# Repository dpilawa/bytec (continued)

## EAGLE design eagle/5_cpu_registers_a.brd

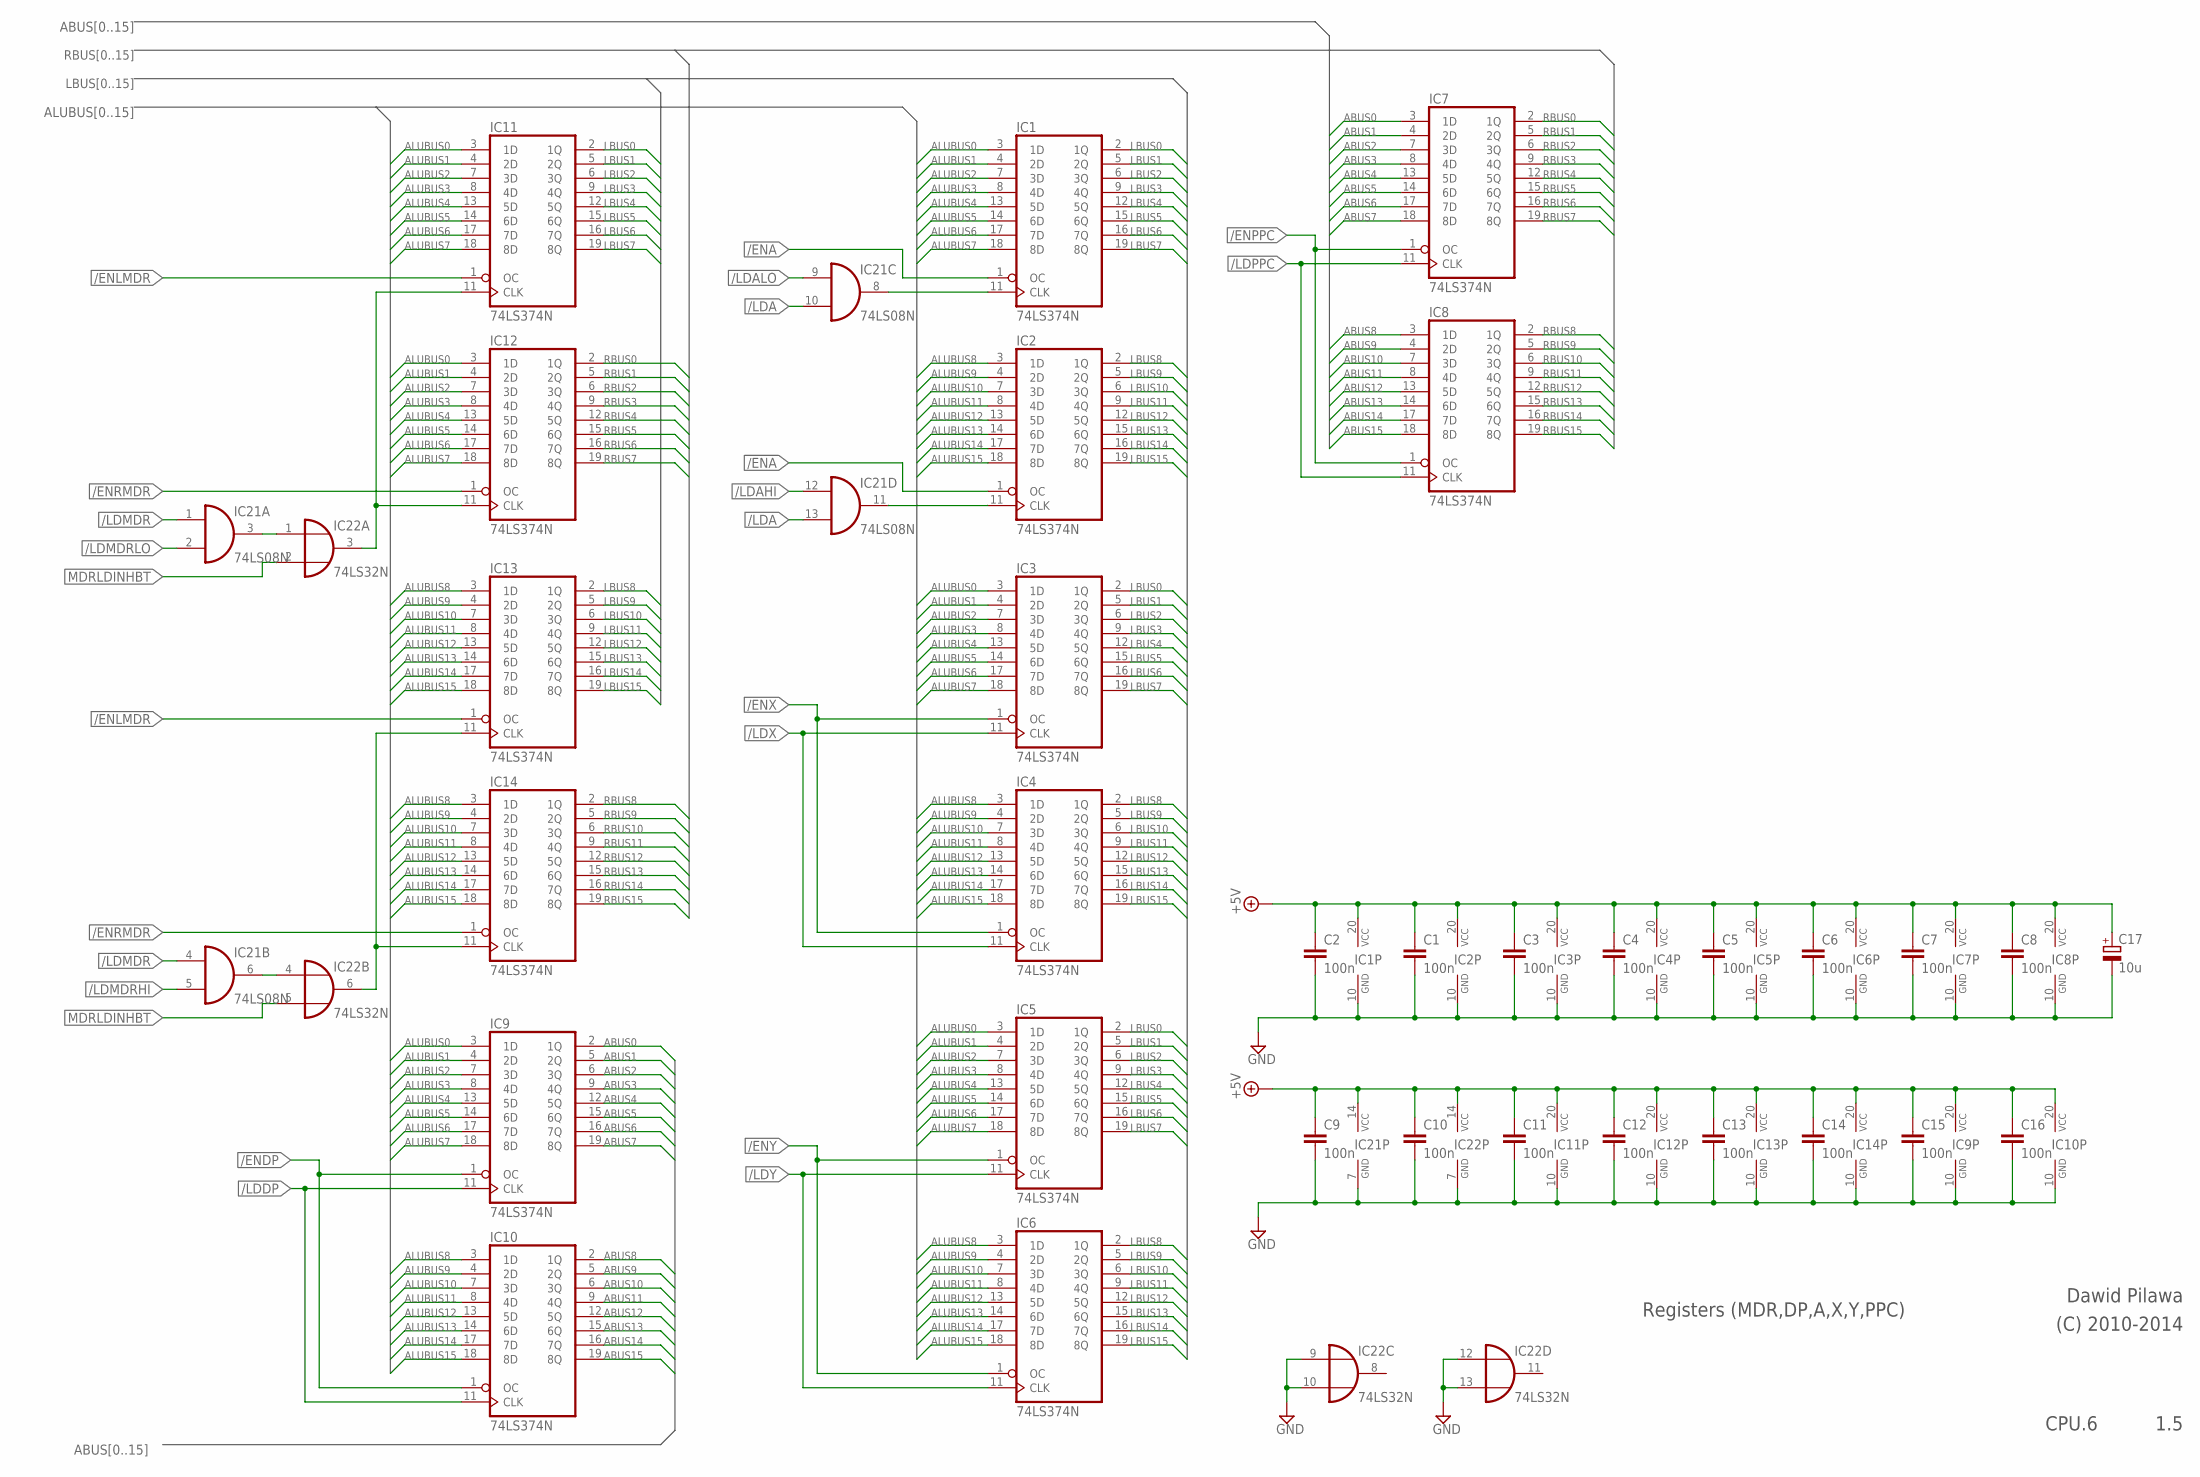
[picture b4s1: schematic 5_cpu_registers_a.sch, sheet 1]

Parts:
C1, C2, C3, C4, C5, C6, C7, C8, C9, C10, C11, C12, C13, C14, C15, C16: 100n; C050-024X044
C17: 10u; E2,5-6
IC1, IC2, IC3, IC4, IC5, IC6, IC7, IC8, IC9, IC10, IC11, IC12, IC13, IC14: 74LS374N; DIL20
IC21: 74LS08N; DIL14
IC22: 74LS32N; DIL14

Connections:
+5V: C1.1, C2.1, C3.1, C4.1, C5.1, C6.1, C7.1, C8.1, C9.1, C10.1, C11.1, C12.1, C13.1, C14.1, C15.1, C16.1, C17.+, IC1.20 (VCC), IC2.20 (VCC), IC3.20 (VCC), IC4.20 (VCC), IC5.20 (VCC), IC6.20 (VCC), IC7.20 (VCC), IC8.20 (VCC), IC9.20 (VCC), IC10.20 (VCC), IC11.20 (VCC), IC12.20 (VCC), IC13.20 (VCC), IC14.20 (VCC), IC21.14 (VCC), IC22.14 (VCC); also elsewhere on the board
/ENA: IC1.1 (OC), IC2.1 (OC); also elsewhere on the board
/ENDP: IC9.1 (OC), IC10.1 (OC); also elsewhere on the board
/ENLMDR: IC11.1 (OC), IC13.1 (OC); also elsewhere on the board
/ENRMDR: IC12.1 (OC), IC14.1 (OC); also elsewhere on the board
/ENX: IC3.1 (OC), IC4.1 (OC); also elsewhere on the board
/ENY: IC5.1 (OC), IC6.1 (OC); also elsewhere on the board
/LDA: IC21.10 (I1), IC21.13 (I1); also elsewhere on the board
/LDAHI: IC21.12 (I0); also elsewhere on the board
/LDALO: IC21.9 (I0); also elsewhere on the board
/LDDP: IC9.11 (CLK), IC10.11 (CLK); also elsewhere on the board
/LDMDR: IC21.1 (I0), IC21.4 (I0); also elsewhere on the board
/LDMDRHI: IC21.5 (I1); also elsewhere on the board
/LDMDRLO: IC21.2 (I1); also elsewhere on the board
/LDX: IC3.11 (CLK), IC4.11 (CLK); also elsewhere on the board
/LDY: IC5.11 (CLK), IC6.11 (CLK); also elsewhere on the board
ABUS0: IC7.3 (1D), IC9.2 (1Q); also elsewhere on the board
ABUS1: IC7.4 (2D), IC9.5 (2Q); also elsewhere on the board
ABUS2: IC7.7 (3D), IC9.6 (3Q); also elsewhere on the board
ABUS3: IC7.8 (4D), IC9.9 (4Q); also elsewhere on the board
ABUS4: IC7.13 (5D), IC9.12 (5Q); also elsewhere on the board
ABUS5: IC7.14 (6D), IC9.15 (6Q); also elsewhere on the board
ABUS6: IC7.17 (7D), IC9.16 (7Q); also elsewhere on the board
ABUS7: IC7.18 (8D), IC9.19 (8Q); also elsewhere on the board
ABUS8: IC8.3 (1D), IC10.2 (1Q); also elsewhere on the board
ABUS9: IC8.4 (2D), IC10.5 (2Q); also elsewhere on the board
ABUS10: IC8.7 (3D), IC10.6 (3Q); also elsewhere on the board
ABUS11: IC8.8 (4D), IC10.9 (4Q); also elsewhere on the board
ABUS12: IC8.13 (5D), IC10.12 (5Q); also elsewhere on the board
ABUS13: IC8.14 (6D), IC10.15 (6Q); also elsewhere on the board
ABUS14: IC8.17 (7D), IC10.16 (7Q); also elsewhere on the board
ABUS15: IC8.18 (8D), IC10.19 (8Q); also elsewhere on the board
ALUBUS0: IC1.3 (1D), IC3.3 (1D), IC5.3 (1D), IC9.3 (1D), IC11.3 (1D), IC12.3 (1D); also elsewhere on the board
ALUBUS1: IC1.4 (2D), IC3.4 (2D), IC5.4 (2D), IC9.4 (2D), IC11.4 (2D), IC12.4 (2D); also elsewhere on the board
ALUBUS2: IC1.7 (3D), IC3.7 (3D), IC5.7 (3D), IC9.7 (3D), IC11.7 (3D), IC12.7 (3D); also elsewhere on the board
ALUBUS3: IC1.8 (4D), IC3.8 (4D), IC5.8 (4D), IC9.8 (4D), IC11.8 (4D), IC12.8 (4D); also elsewhere on the board
ALUBUS4: IC1.13 (5D), IC3.13 (5D), IC5.13 (5D), IC9.13 (5D), IC11.13 (5D), IC12.13 (5D); also elsewhere on the board
ALUBUS5: IC1.14 (6D), IC3.14 (6D), IC5.14 (6D), IC9.14 (6D), IC11.14 (6D), IC12.14 (6D); also elsewhere on the board
ALUBUS6: IC1.17 (7D), IC3.17 (7D), IC5.17 (7D), IC9.17 (7D), IC11.17 (7D), IC12.17 (7D); also elsewhere on the board
ALUBUS7: IC1.18 (8D), IC3.18 (8D), IC5.18 (8D), IC9.18 (8D), IC11.18 (8D), IC12.18 (8D); also elsewhere on the board
ALUBUS8: IC2.3 (1D), IC4.3 (1D), IC6.3 (1D), IC10.3 (1D), IC13.3 (1D), IC14.3 (1D); also elsewhere on the board
ALUBUS9: IC2.4 (2D), IC4.4 (2D), IC6.4 (2D), IC10.4 (2D), IC13.4 (2D), IC14.4 (2D); also elsewhere on the board
ALUBUS10: IC2.7 (3D), IC4.7 (3D), IC6.7 (3D), IC10.7 (3D), IC13.7 (3D), IC14.7 (3D); also elsewhere on the board
ALUBUS11: IC2.8 (4D), IC4.8 (4D), IC6.8 (4D), IC10.8 (4D), IC13.8 (4D), IC14.8 (4D); also elsewhere on the board
ALUBUS12: IC2.13 (5D), IC4.13 (5D), IC6.13 (5D), IC10.13 (5D), IC13.13 (5D), IC14.13 (5D); also elsewhere on the board
ALUBUS13: IC2.14 (6D), IC4.14 (6D), IC6.14 (6D), IC10.14 (6D), IC13.14 (6D), IC14.14 (6D); also elsewhere on the board
ALUBUS14: IC2.17 (7D), IC4.17 (7D), IC6.17 (7D), IC10.17 (7D), IC13.17 (7D), IC14.17 (7D); also elsewhere on the board
ALUBUS15: IC2.18 (8D), IC4.18 (8D), IC6.18 (8D), IC10.18 (8D), IC13.18 (8D), IC14.18 (8D); also elsewhere on the board
GND: C1.2, C2.2, C3.2, C4.2, C5.2, C6.2, C7.2, C8.2, C9.2, C10.2, C11.2, C12.2, C13.2, C14.2, C15.2, C16.2, C17.-, IC1.10 (GND), IC2.10 (GND), IC3.10 (GND), IC4.10 (GND), IC5.10 (GND), IC6.10 (GND), IC7.10 (GND), IC8.10 (GND), IC9.10 (GND), IC10.10 (GND), IC11.10 (GND), IC12.10 (GND), IC13.10 (GND), IC14.10 (GND), IC21.7 (GND), IC22.7 (GND), IC22.9 (I0), IC22.10 (I1), IC22.12 (I0), IC22.13 (I1); also elsewhere on the board
LBUS0: IC1.2 (1Q), IC3.2 (1Q), IC5.2 (1Q), IC11.2 (1Q); also elsewhere on the board
LBUS1: IC1.5 (2Q), IC3.5 (2Q), IC5.5 (2Q), IC11.5 (2Q); also elsewhere on the board
LBUS2: IC1.6 (3Q), IC3.6 (3Q), IC5.6 (3Q), IC11.6 (3Q); also elsewhere on the board
LBUS3: IC1.9 (4Q), IC3.9 (4Q), IC5.9 (4Q), IC11.9 (4Q); also elsewhere on the board
LBUS4: IC1.12 (5Q), IC3.12 (5Q), IC5.12 (5Q), IC11.12 (5Q); also elsewhere on the board
LBUS5: IC1.15 (6Q), IC3.15 (6Q), IC5.15 (6Q), IC11.15 (6Q); also elsewhere on the board
LBUS6: IC1.16 (7Q), IC3.16 (7Q), IC5.16 (7Q), IC11.16 (7Q); also elsewhere on the board
LBUS7: IC1.19 (8Q), IC3.19 (8Q), IC5.19 (8Q), IC11.19 (8Q); also elsewhere on the board
LBUS8: IC2.2 (1Q), IC4.2 (1Q), IC6.2 (1Q), IC13.2 (1Q); also elsewhere on the board
LBUS9: IC2.5 (2Q), IC4.5 (2Q), IC6.5 (2Q), IC13.5 (2Q); also elsewhere on the board
LBUS10: IC2.6 (3Q), IC4.6 (3Q), IC6.6 (3Q), IC13.6 (3Q); also elsewhere on the board
LBUS11: IC2.9 (4Q), IC4.9 (4Q), IC6.9 (4Q), IC13.9 (4Q); also elsewhere on the board
LBUS12: IC2.12 (5Q), IC4.12 (5Q), IC6.12 (5Q), IC13.12 (5Q); also elsewhere on the board
LBUS13: IC2.15 (6Q), IC4.15 (6Q), IC6.15 (6Q), IC13.15 (6Q); also elsewhere on the board
LBUS14: IC2.16 (7Q), IC4.16 (7Q), IC6.16 (7Q), IC13.16 (7Q); also elsewhere on the board
LBUS15: IC2.19 (8Q), IC4.19 (8Q), IC6.19 (8Q), IC13.19 (8Q); also elsewhere on the board
MDRLDINHBT: IC22.2 (I1), IC22.5 (I1); also elsewhere on the board
unnamed: IC11.11 (CLK), IC12.11 (CLK), IC22.3 (O)
unnamed: IC21.3 (O), IC22.1 (I0)
unnamed: IC21.6 (O), IC22.4 (I0)
unnamed: IC13.11 (CLK), IC14.11 (CLK), IC22.6 (O)
unnamed: IC1.11 (CLK), IC21.8 (O)
unnamed: IC2.11 (CLK), IC21.11 (O)
unnamed: IC7.1 (OC), IC8.1 (OC)
unnamed: IC7.11 (CLK), IC8.11 (CLK)
RBUS0: IC7.2 (1Q), IC12.2 (1Q); also elsewhere on the board
RBUS1: IC7.5 (2Q), IC12.5 (2Q); also elsewhere on the board
RBUS2: IC7.6 (3Q), IC12.6 (3Q); also elsewhere on the board
RBUS3: IC7.9 (4Q), IC12.9 (4Q); also elsewhere on the board
RBUS4: IC7.12 (5Q), IC12.12 (5Q); also elsewhere on the board
RBUS5: IC7.15 (6Q), IC12.15 (6Q); also elsewhere on the board
RBUS6: IC7.16 (7Q), IC12.16 (7Q); also elsewhere on the board
RBUS7: IC7.19 (8Q), IC12.19 (8Q); also elsewhere on the board
RBUS8: IC8.2 (1Q), IC14.2 (1Q); also elsewhere on the board
RBUS9: IC8.5 (2Q), IC14.5 (2Q); also elsewhere on the board
RBUS10: IC8.6 (3Q), IC14.6 (3Q); also elsewhere on the board
RBUS11: IC8.9 (4Q), IC14.9 (4Q); also elsewhere on the board
RBUS12: IC8.12 (5Q), IC14.12 (5Q); also elsewhere on the board
RBUS13: IC8.15 (6Q), IC14.15 (6Q); also elsewhere on the board
RBUS14: IC8.16 (7Q), IC14.16 (7Q); also elsewhere on the board
RBUS15: IC8.19 (8Q), IC14.19 (8Q); also elsewhere on the board

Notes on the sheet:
Registers (MDR,DP,A,X,Y,PPC)
Dawid Pilawa
(C) 2010-2014
CPU.6
1.5

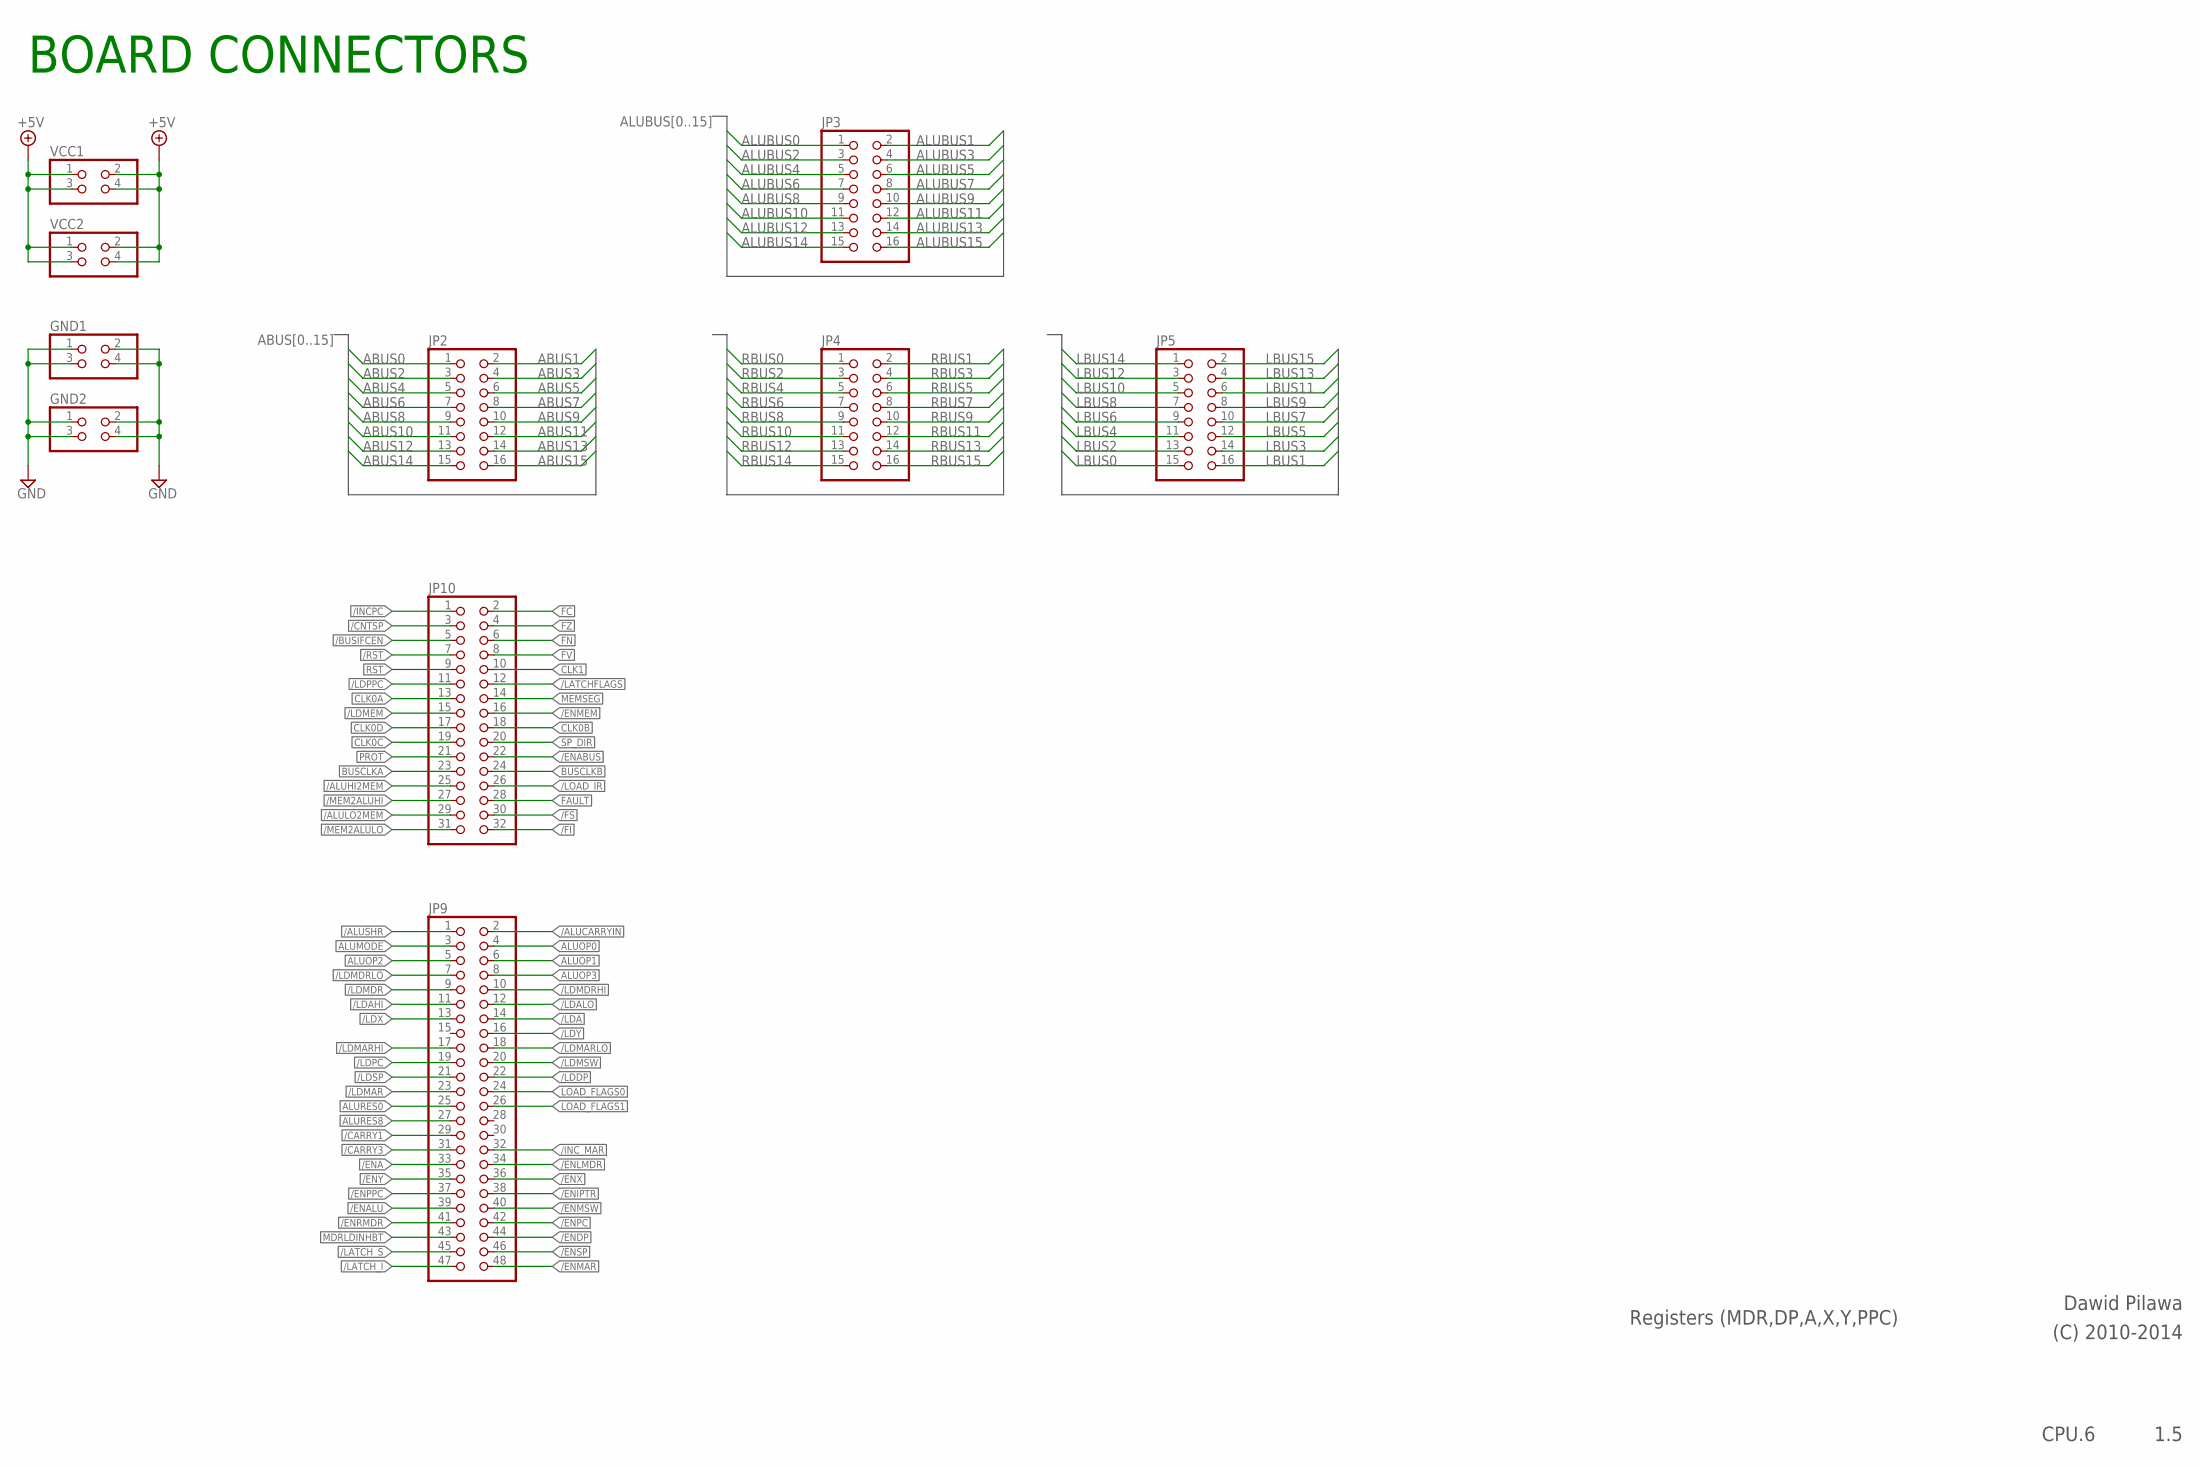
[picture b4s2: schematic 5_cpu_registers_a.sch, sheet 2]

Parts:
GND1, GND2: PINHD-2X2; 2X02
JP2, JP3, JP4, JP5: PINHD-2X8; 2X08
JP9: PINHD-2X24; 2X24
JP10: PINHD-2X16; 2X16
VCC1, VCC2: PINHD-2X2; 2X02

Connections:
+5V: VCC1.1, VCC1.2, VCC1.3, VCC1.4, VCC2.1, VCC2.2, VCC2.3, VCC2.4; also elsewhere on the board
/ALUCARRYIN: JP9.2
/ALUHI2MEM: JP10.25
/ALULO2MEM: JP10.29
/ALUSHR: JP9.1
/BUSIFCEN: JP10.5
/CARRY1: JP9.29
/CARRY3: JP9.31
/CNTSP: JP10.3
/ENA: JP9.33; also elsewhere on the board
/ENABUS: JP10.22
/ENALU: JP9.39
/ENDP: JP9.44; also elsewhere on the board
/ENIPTR: JP9.38
/ENLMDR: JP9.34; also elsewhere on the board
/ENMAR: JP9.48
/ENMEM: JP10.16
/ENMSW: JP9.40
/ENPC: JP9.42
/ENRMDR: JP9.41; also elsewhere on the board
/ENSP: JP9.46
/ENX: JP9.36; also elsewhere on the board
/ENY: JP9.35; also elsewhere on the board
/FI: JP10.32
/FS: JP10.30
/INCPC: JP10.1
/INC_MAR: JP9.32
/LATCHFLAGS: JP10.12
/LATCH_I: JP9.47
/LATCH_S: JP9.45
/LDA: JP9.14; also elsewhere on the board
/LDAHI: JP9.11; also elsewhere on the board
/LDALO: JP9.12; also elsewhere on the board
/LDDP: JP9.22; also elsewhere on the board
/LDMAR: JP9.23
/LDMARHI: JP9.17
/LDMARLO: JP9.18
/LDMDR: JP9.9; also elsewhere on the board
/LDMDRHI: JP9.10; also elsewhere on the board
/LDMDRLO: JP9.7; also elsewhere on the board
/LDMEM: JP10.15
/LDMSW: JP9.20
/LDPC: JP9.19
/LDSP: JP9.21
/LDX: JP9.13; also elsewhere on the board
/LDY: JP9.16; also elsewhere on the board
/LOAD_IR: JP10.26
/MEM2ALUHI: JP10.27
/MEM2ALULO: JP10.31
/RST: JP10.7
ABUS0: JP2.1; also elsewhere on the board
ABUS1: JP2.2; also elsewhere on the board
ABUS2: JP2.3; also elsewhere on the board
ABUS3: JP2.4; also elsewhere on the board
ABUS4: JP2.5; also elsewhere on the board
ABUS5: JP2.6; also elsewhere on the board
ABUS6: JP2.7; also elsewhere on the board
ABUS7: JP2.8; also elsewhere on the board
ABUS8: JP2.9; also elsewhere on the board
ABUS9: JP2.10; also elsewhere on the board
ABUS10: JP2.11; also elsewhere on the board
ABUS11: JP2.12; also elsewhere on the board
ABUS12: JP2.13; also elsewhere on the board
ABUS13: JP2.14; also elsewhere on the board
ABUS14: JP2.15; also elsewhere on the board
ABUS15: JP2.16; also elsewhere on the board
ALUBUS0: JP3.1; also elsewhere on the board
ALUBUS1: JP3.2; also elsewhere on the board
ALUBUS2: JP3.3; also elsewhere on the board
ALUBUS3: JP3.4; also elsewhere on the board
ALUBUS4: JP3.5; also elsewhere on the board
ALUBUS5: JP3.6; also elsewhere on the board
ALUBUS6: JP3.7; also elsewhere on the board
ALUBUS7: JP3.8; also elsewhere on the board
ALUBUS8: JP3.9; also elsewhere on the board
ALUBUS9: JP3.10; also elsewhere on the board
ALUBUS10: JP3.11; also elsewhere on the board
ALUBUS11: JP3.12; also elsewhere on the board
ALUBUS12: JP3.13; also elsewhere on the board
ALUBUS13: JP3.14; also elsewhere on the board
ALUBUS14: JP3.15; also elsewhere on the board
ALUBUS15: JP3.16; also elsewhere on the board
ALUMODE: JP9.3
ALUOP0: JP9.4
ALUOP1: JP9.6
ALUOP2: JP9.5
ALUOP3: JP9.8
ALURES0: JP9.25
ALURES8: JP9.27
BUSCLKA: JP10.23
BUSCLKB: JP10.24
CLK0A: JP10.13
CLK0B: JP10.18
CLK0C: JP10.19
CLK0D: JP10.17
CLK1: JP10.10
FAULT: JP10.28
FC: JP10.2
FN: JP10.6
FV: JP10.8
FZ: JP10.4
GND: GND1.1, GND1.2, GND1.3, GND1.4, GND2.1, GND2.2, GND2.3, GND2.4; also elsewhere on the board
LBUS0: JP5.15; also elsewhere on the board
LBUS1: JP5.16; also elsewhere on the board
LBUS2: JP5.13; also elsewhere on the board
LBUS3: JP5.14; also elsewhere on the board
LBUS4: JP5.11; also elsewhere on the board
LBUS5: JP5.12; also elsewhere on the board
LBUS6: JP5.9; also elsewhere on the board
LBUS7: JP5.10; also elsewhere on the board
LBUS8: JP5.7; also elsewhere on the board
LBUS9: JP5.8; also elsewhere on the board
LBUS10: JP5.5; also elsewhere on the board
LBUS11: JP5.6; also elsewhere on the board
LBUS12: JP5.3; also elsewhere on the board
LBUS13: JP5.4; also elsewhere on the board
LBUS14: JP5.1; also elsewhere on the board
LBUS15: JP5.2; also elsewhere on the board
LOAD_FLAGS0: JP9.24
LOAD_FLAGS1: JP9.26
MDRLDINHBT: JP9.43; also elsewhere on the board
MEMSEG: JP10.14
PROT: JP10.21
RBUS0: JP4.1; also elsewhere on the board
RBUS1: JP4.2; also elsewhere on the board
RBUS2: JP4.3; also elsewhere on the board
RBUS3: JP4.4; also elsewhere on the board
RBUS4: JP4.5; also elsewhere on the board
RBUS5: JP4.6; also elsewhere on the board
RBUS6: JP4.7; also elsewhere on the board
RBUS7: JP4.8; also elsewhere on the board
RBUS8: JP4.9; also elsewhere on the board
RBUS9: JP4.10; also elsewhere on the board
RBUS10: JP4.11; also elsewhere on the board
RBUS11: JP4.12; also elsewhere on the board
RBUS12: JP4.13; also elsewhere on the board
RBUS13: JP4.14; also elsewhere on the board
RBUS14: JP4.15; also elsewhere on the board
RBUS15: JP4.16; also elsewhere on the board
RST: JP10.9
SP_DIR: JP10.20

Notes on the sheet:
Registers (MDR,DP,A,X,Y,PPC)
Dawid Pilawa
(C) 2010-2014
CPU.6
1.5
BOARD CONNECTORS

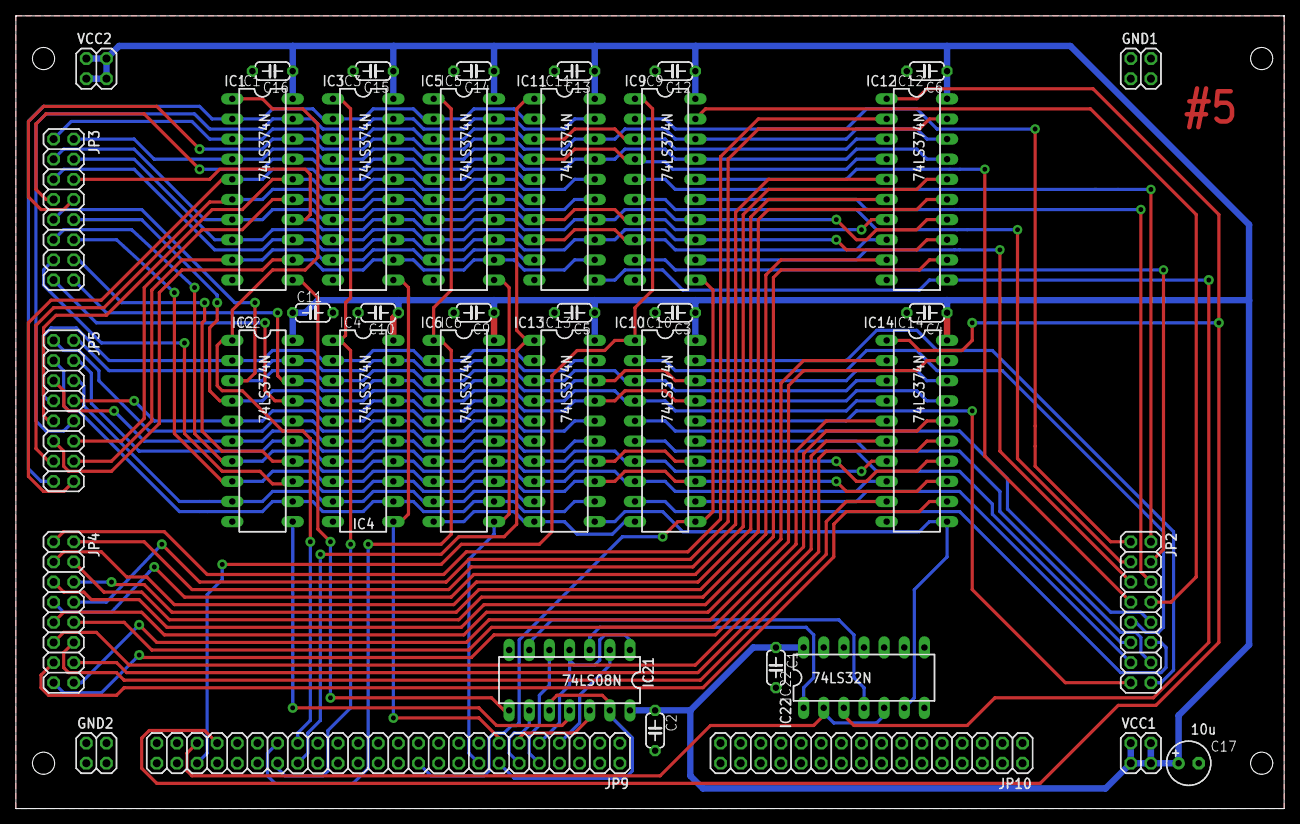
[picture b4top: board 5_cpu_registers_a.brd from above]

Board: 2 copper layers, 160.0 x 100.0 mm, 39 parts (0 on the bottom side), 88 nets.

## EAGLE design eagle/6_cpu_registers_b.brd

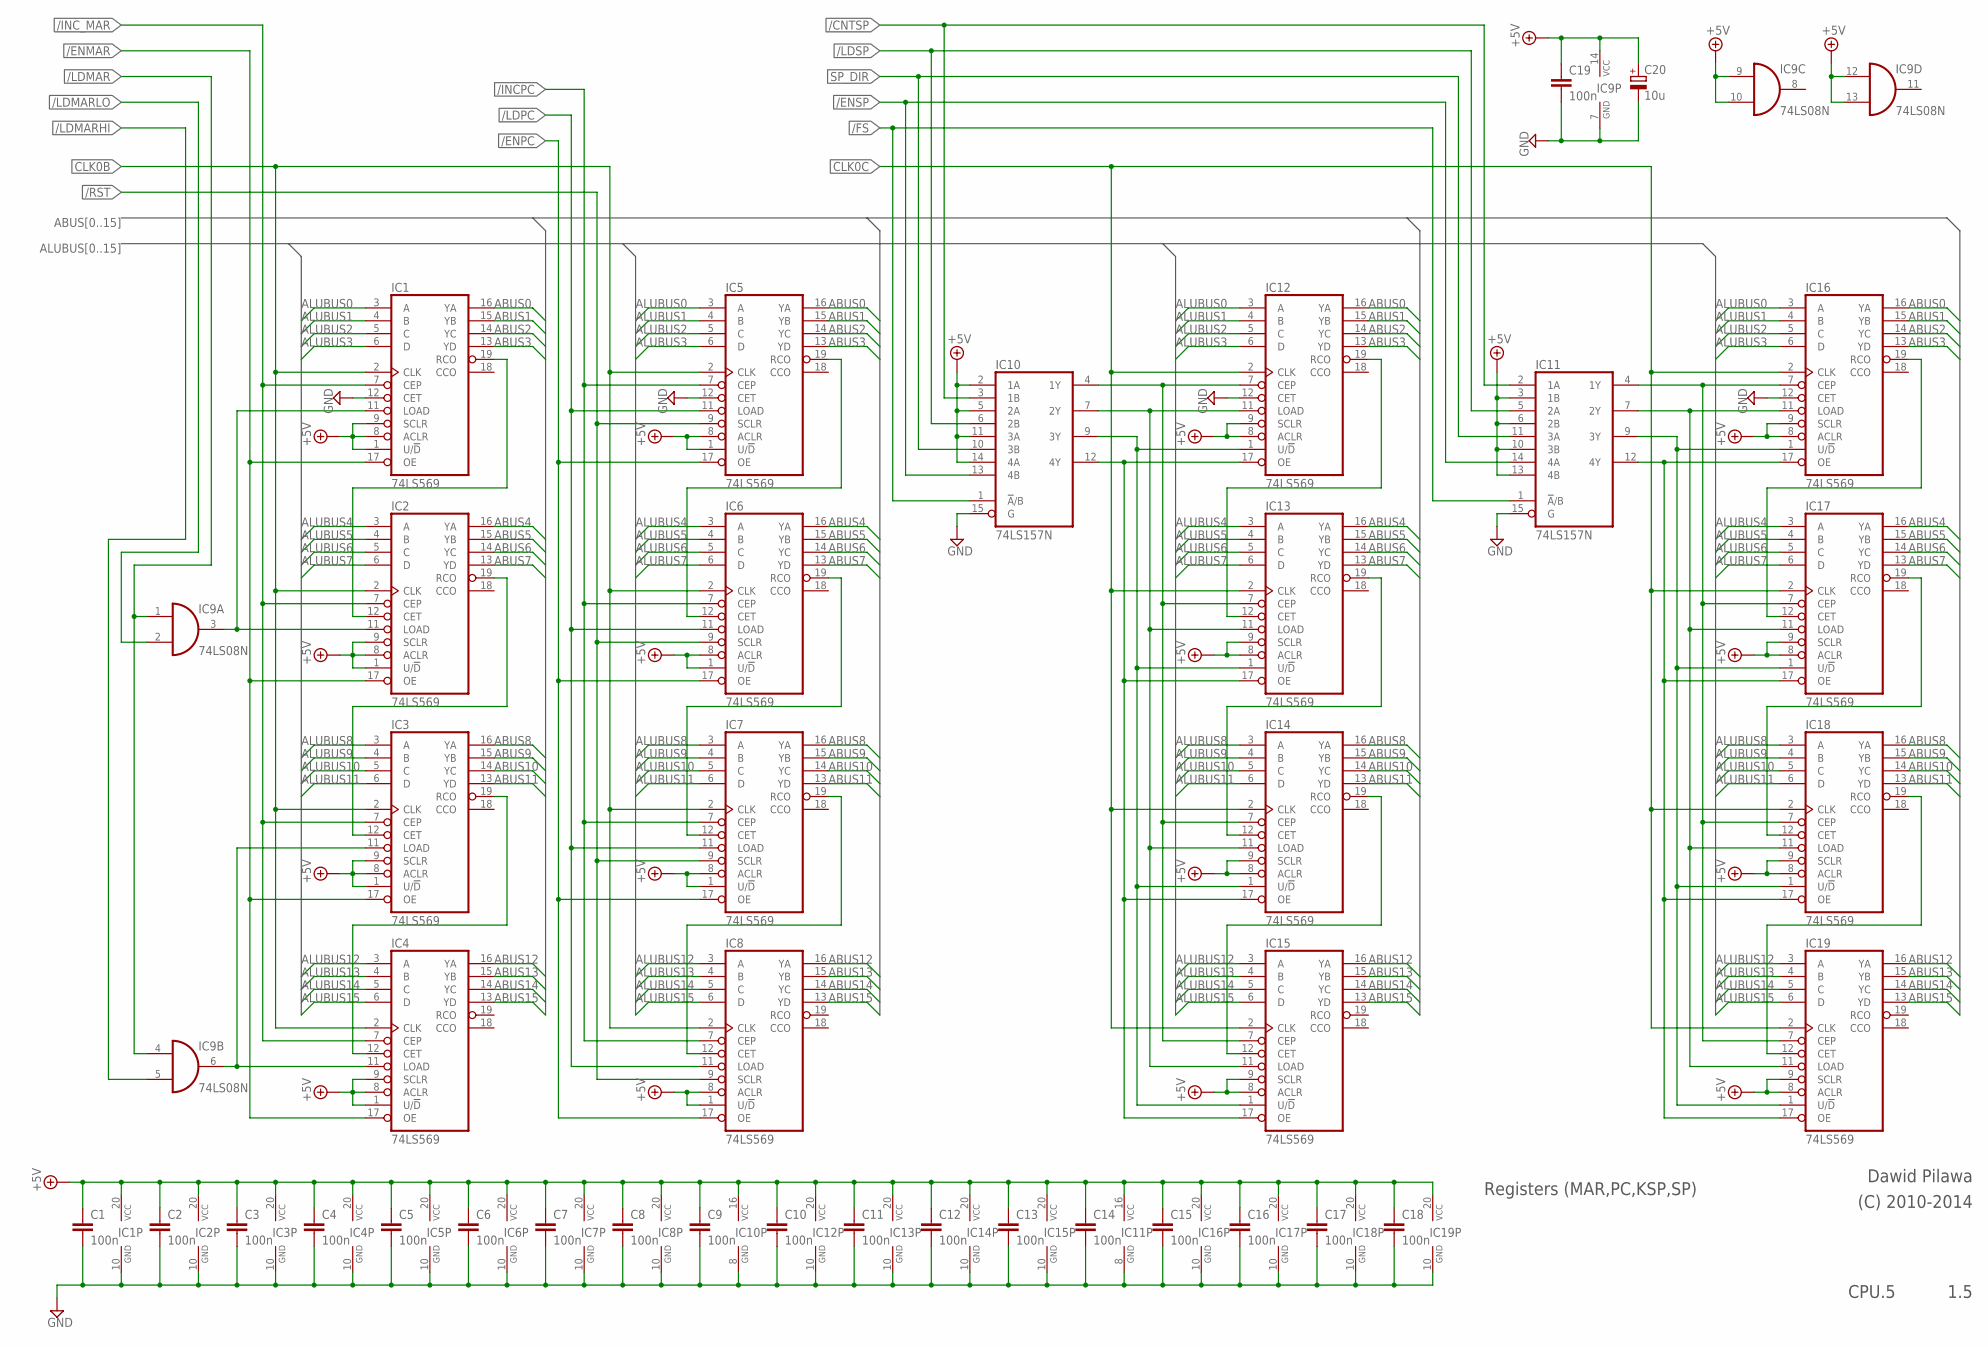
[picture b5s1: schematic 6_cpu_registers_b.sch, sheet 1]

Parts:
C1, C2, C3, C4, C5, C6, C7, C8, C9, C10, C11, C12, C13, C14, C15, C16, C17, C18, C19: 100n; C050-024X044
C20: 10u; E2,5-6
IC1, IC2, IC3, IC4, IC5, IC6, IC7, IC8, IC12, IC13, IC14, IC15, IC16, IC17, IC18, IC19: 74LS569; DIL20
IC9: 74LS08N; DIL14
IC10, IC11: 74LS157N; DIL16

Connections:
+5V: C1.1, C2.1, C3.1, C4.1, C5.1, C6.1, C7.1, C8.1, C9.1, C10.1, C11.1, C12.1, C13.1, C14.1, C15.1, C16.1, C17.1, C18.1, C19.1, C20.+, IC1.1 (U/!D), IC1.8 (ACLR), IC1.9 (SCLR), IC1.20 (VCC), IC2.1 (U/!D), IC2.8 (ACLR), IC2.9 (SCLR), IC2.20 (VCC), IC3.1 (U/!D), IC3.8 (ACLR), IC3.9 (SCLR), IC3.20 (VCC), IC4.1 (U/!D), IC4.8 (ACLR), IC4.9 (SCLR), IC4.20 (VCC), IC5.1 (U/!D), IC5.8 (ACLR), IC5.20 (VCC), IC6.1 (U/!D), IC6.8 (ACLR), IC6.20 (VCC), IC7.1 (U/!D), IC7.8 (ACLR), IC7.20 (VCC), IC8.1 (U/!D), IC8.8 (ACLR), IC8.20 (VCC), IC9.9 (I0), IC9.10 (I1), IC9.12 (I0), IC9.13 (I1), IC9.14 (VCC), IC10.2 (1A), IC10.5 (2A), IC10.11 (3A), IC10.14 (4A), IC10.16 (VCC), IC11.3 (1B), IC11.6 (2B), IC11.10 (3B), IC11.13 (4B), IC11.16 (VCC), IC12.8 (ACLR), IC12.9 (SCLR), IC12.20 (VCC), IC13.8 (ACLR), IC13.9 (SCLR), IC13.20 (VCC), IC14.8 (ACLR), IC14.9 (SCLR), IC14.20 (VCC), IC15.8 (ACLR), IC15.9 (SCLR), IC15.20 (VCC), IC16.8 (ACLR), IC16.9 (SCLR), IC16.20 (VCC), IC17.8 (ACLR), IC17.9 (SCLR), IC17.20 (VCC), IC18.8 (ACLR), IC18.9 (SCLR), IC18.20 (VCC), IC19.8 (ACLR), IC19.9 (SCLR), IC19.20 (VCC); also elsewhere on the board
/CNTSP: IC10.3 (1B), IC11.2 (1A); also elsewhere on the board
/ENMAR: IC1.17 (OE), IC2.17 (OE), IC3.17 (OE), IC4.17 (OE); also elsewhere on the board
/ENPC: IC5.17 (OE), IC6.17 (OE), IC7.17 (OE), IC8.17 (OE); also elsewhere on the board
/ENSP: IC10.13 (4B), IC11.14 (4A); also elsewhere on the board
/FS: IC10.1 (!A!/B), IC11.1 (!A!/B); also elsewhere on the board
/INCPC: IC5.7 (CEP), IC6.7 (CEP), IC7.7 (CEP), IC8.7 (CEP); also elsewhere on the board
/INC_MAR: IC1.7 (CEP), IC2.7 (CEP), IC3.7 (CEP), IC4.7 (CEP); also elsewhere on the board
/LDMAR: IC9.1 (I0), IC9.4 (I0); also elsewhere on the board
/LDMARHI: IC9.5 (I1); also elsewhere on the board
/LDMARLO: IC9.2 (I1); also elsewhere on the board
/LDPC: IC5.11 (LOAD), IC6.11 (LOAD), IC7.11 (LOAD), IC8.11 (LOAD); also elsewhere on the board
/LDSP: IC10.6 (2B), IC11.5 (2A); also elsewhere on the board
/RST: IC5.9 (SCLR), IC6.9 (SCLR), IC7.9 (SCLR), IC8.9 (SCLR); also elsewhere on the board
ABUS0: IC1.16 (YA), IC5.16 (YA), IC12.16 (YA), IC16.16 (YA); also elsewhere on the board
ABUS1: IC1.15 (YB), IC5.15 (YB), IC12.15 (YB), IC16.15 (YB); also elsewhere on the board
ABUS2: IC1.14 (YC), IC5.14 (YC), IC12.14 (YC), IC16.14 (YC); also elsewhere on the board
ABUS3: IC1.13 (YD), IC5.13 (YD), IC12.13 (YD), IC16.13 (YD); also elsewhere on the board
ABUS4: IC2.16 (YA), IC6.16 (YA), IC13.16 (YA), IC17.16 (YA); also elsewhere on the board
ABUS5: IC2.15 (YB), IC6.15 (YB), IC13.15 (YB), IC17.15 (YB); also elsewhere on the board
ABUS6: IC2.14 (YC), IC6.14 (YC), IC13.14 (YC), IC17.14 (YC); also elsewhere on the board
ABUS7: IC2.13 (YD), IC6.13 (YD), IC13.13 (YD), IC17.13 (YD); also elsewhere on the board
ABUS8: IC3.16 (YA), IC7.16 (YA), IC14.16 (YA), IC18.16 (YA); also elsewhere on the board
ABUS9: IC3.15 (YB), IC7.15 (YB), IC14.15 (YB), IC18.15 (YB); also elsewhere on the board
ABUS10: IC3.14 (YC), IC7.14 (YC), IC14.14 (YC), IC18.14 (YC); also elsewhere on the board
ABUS11: IC3.13 (YD), IC7.13 (YD), IC14.13 (YD), IC18.13 (YD); also elsewhere on the board
ABUS12: IC4.16 (YA), IC8.16 (YA), IC15.16 (YA), IC19.16 (YA); also elsewhere on the board
ABUS13: IC4.15 (YB), IC8.15 (YB), IC15.15 (YB), IC19.15 (YB); also elsewhere on the board
ABUS14: IC4.14 (YC), IC8.14 (YC), IC15.14 (YC), IC19.14 (YC); also elsewhere on the board
ABUS15: IC4.13 (YD), IC8.13 (YD), IC15.13 (YD), IC19.13 (YD); also elsewhere on the board
ALUBUS0: IC1.3 (A), IC5.3 (A), IC12.3 (A), IC16.3 (A); also elsewhere on the board
ALUBUS1: IC1.4 (B), IC5.4 (B), IC12.4 (B), IC16.4 (B); also elsewhere on the board
ALUBUS2: IC1.5 (C), IC5.5 (C), IC12.5 (C), IC16.5 (C); also elsewhere on the board
ALUBUS3: IC1.6 (D), IC5.6 (D), IC12.6 (D), IC16.6 (D); also elsewhere on the board
ALUBUS4: IC2.3 (A), IC6.3 (A), IC13.3 (A), IC17.3 (A); also elsewhere on the board
ALUBUS5: IC2.4 (B), IC6.4 (B), IC13.4 (B), IC17.4 (B); also elsewhere on the board
ALUBUS6: IC2.5 (C), IC6.5 (C), IC13.5 (C), IC17.5 (C); also elsewhere on the board
ALUBUS7: IC2.6 (D), IC6.6 (D), IC13.6 (D), IC17.6 (D); also elsewhere on the board
ALUBUS8: IC3.3 (A), IC7.3 (A), IC14.3 (A), IC18.3 (A); also elsewhere on the board
ALUBUS9: IC3.4 (B), IC7.4 (B), IC14.4 (B), IC18.4 (B); also elsewhere on the board
ALUBUS10: IC3.5 (C), IC7.5 (C), IC14.5 (C), IC18.5 (C); also elsewhere on the board
ALUBUS11: IC3.6 (D), IC7.6 (D), IC14.6 (D), IC18.6 (D); also elsewhere on the board
ALUBUS12: IC4.3 (A), IC8.3 (A), IC15.3 (A), IC19.3 (A); also elsewhere on the board
ALUBUS13: IC4.4 (B), IC8.4 (B), IC15.4 (B), IC19.4 (B); also elsewhere on the board
ALUBUS14: IC4.5 (C), IC8.5 (C), IC15.5 (C), IC19.5 (C); also elsewhere on the board
ALUBUS15: IC4.6 (D), IC8.6 (D), IC15.6 (D), IC19.6 (D); also elsewhere on the board
CLK0B: IC1.2 (CLK), IC2.2 (CLK), IC3.2 (CLK), IC4.2 (CLK), IC5.2 (CLK), IC6.2 (CLK), IC7.2 (CLK), IC8.2 (CLK); also elsewhere on the board
CLK0C: IC12.2 (CLK), IC13.2 (CLK), IC14.2 (CLK), IC15.2 (CLK), IC16.2 (CLK), IC17.2 (CLK), IC18.2 (CLK), IC19.2 (CLK); also elsewhere on the board
GND: C1.2, C2.2, C3.2, C4.2, C5.2, C6.2, C7.2, C8.2, C9.2, C10.2, C11.2, C12.2, C13.2, C14.2, C15.2, C16.2, C17.2, C18.2, C19.2, C20.-, IC1.10 (GND), IC1.12 (CET), IC2.10 (GND), IC3.10 (GND), IC4.10 (GND), IC5.10 (GND), IC5.12 (CET), IC6.10 (GND), IC7.10 (GND), IC8.10 (GND), IC9.7 (GND), IC10.8 (GND), IC10.15 (G), IC11.8 (GND), IC11.15 (G), IC12.10 (GND), IC12.12 (CET), IC13.10 (GND), IC14.10 (GND), IC15.10 (GND), IC16.10 (GND), IC16.12 (CET), IC17.10 (GND), IC18.10 (GND), IC19.10 (GND); also elsewhere on the board
unnamed: IC1.11 (LOAD), IC2.11 (LOAD), IC9.3 (O)
unnamed: IC6.19 (RCO), IC7.12 (CET)
unnamed: IC5.19 (RCO), IC6.12 (CET)
unnamed: IC7.19 (RCO), IC8.12 (CET)
unnamed: IC12.19 (RCO), IC13.12 (CET)
unnamed: IC13.19 (RCO), IC14.12 (CET)
unnamed: IC3.11 (LOAD), IC4.11 (LOAD), IC9.6 (O)
unnamed: IC14.19 (RCO), IC15.12 (CET)
unnamed: IC10.4 (1Y), IC12.7 (CEP), IC13.7 (CEP), IC14.7 (CEP), IC15.7 (CEP)
unnamed: IC1.19 (RCO), IC2.12 (CET)
unnamed: IC2.19 (RCO), IC3.12 (CET)
unnamed: IC3.19 (RCO), IC4.12 (CET)
unnamed: IC10.7 (2Y), IC12.11 (LOAD), IC13.11 (LOAD), IC14.11 (LOAD), IC15.11 (LOAD)
unnamed: IC10.9 (3Y), IC12.1 (U/!D), IC13.1 (U/!D), IC14.1 (U/!D), IC15.1 (U/!D)
unnamed: IC11.9 (3Y), IC16.1 (U/!D), IC17.1 (U/!D), IC18.1 (U/!D), IC19.1 (U/!D)
unnamed: IC10.12 (4Y), IC12.17 (OE), IC13.17 (OE), IC14.17 (OE), IC15.17 (OE)
unnamed: IC11.12 (4Y), IC16.17 (OE), IC17.17 (OE), IC18.17 (OE), IC19.17 (OE)
unnamed: IC16.19 (RCO), IC17.12 (CET)
unnamed: IC17.19 (RCO), IC18.12 (CET)
unnamed: IC18.19 (RCO), IC19.12 (CET)
unnamed: IC11.4 (1Y), IC16.7 (CEP), IC17.7 (CEP), IC18.7 (CEP), IC19.7 (CEP)
unnamed: IC11.7 (2Y), IC16.11 (LOAD), IC17.11 (LOAD), IC18.11 (LOAD), IC19.11 (LOAD)
SP_DIR: IC10.10 (3B), IC11.11 (3A); also elsewhere on the board

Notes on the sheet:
Registers (MAR,PC,KSP,SP)
Dawid Pilawa
(C) 2010-2014
CPU.5
1.5
